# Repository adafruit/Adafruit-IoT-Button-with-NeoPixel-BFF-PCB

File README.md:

## Adafruit IoT Button with NeoPixel BFF PCB

<a href="http://www.adafruit.com/products/5666"><br/>
Click here to purchase one from the Adafruit shop</a>

PCB files for the Adafruit IoT Button with NeoPixel BFF. 

Format is EagleCAD schematic and board layout
* https://www.adafruit.com/product/5666

### Description

Our QT Py boards are a great way to make very small microcontroller projects that pack a ton of power - and now we have a way for you to quickly add a chunky 12mm tactile button with a NeoPixel. It's an excellent way to create simple 'IoT Button' type projects with basic interactivity.

We call this the Adafruit IoT Button with NeoPixel BFF - a "Best Friend Forever". When you were a kid you may have learned about the "buddy" system, well this product is kinda like that! A board that will watch your QT Py's back and give it more capabilities.

This PCB is designed to fit onto the back of any QT Py or Xiao board, it can be soldered into place or use pin and socket headers to make it removable. Onboard is a 12mm tactile button with a nice large actuator, above is a 3.5mm RGB NeoPixel.

We include some header that you can solder to your QT Py. You can also pick up an Itsy Bitsy short female header kit to make it removable but compact, you'll just need to trim down the headers to 7 pins long.

Comes as an assembled and tested PCB
For any QT Py or Xiao boards
Tactile switch momentarily connects A2  to ground when pressed - can cut/re-wire an onboard jumper to change pins if desired. Don't forget to enable an internal pull-up resistor on A2 or whatever pin you use.,
Single NeoPixel on GPIO A3 - can cut/re-wire an onboard jumper to change pins if desired.
QT Py is not included.

### License

Adafruit invests time and resources providing this open source design, please support Adafruit and open-source hardware by purchasing products from [Adafruit](https://www.adafruit.com)!

Designed by Limor Fried/Ladyada for Adafruit Industries.

Creative Commons Attribution/Share-Alike, all text above must be included in any redistribution. 
See license.txt for additional details.

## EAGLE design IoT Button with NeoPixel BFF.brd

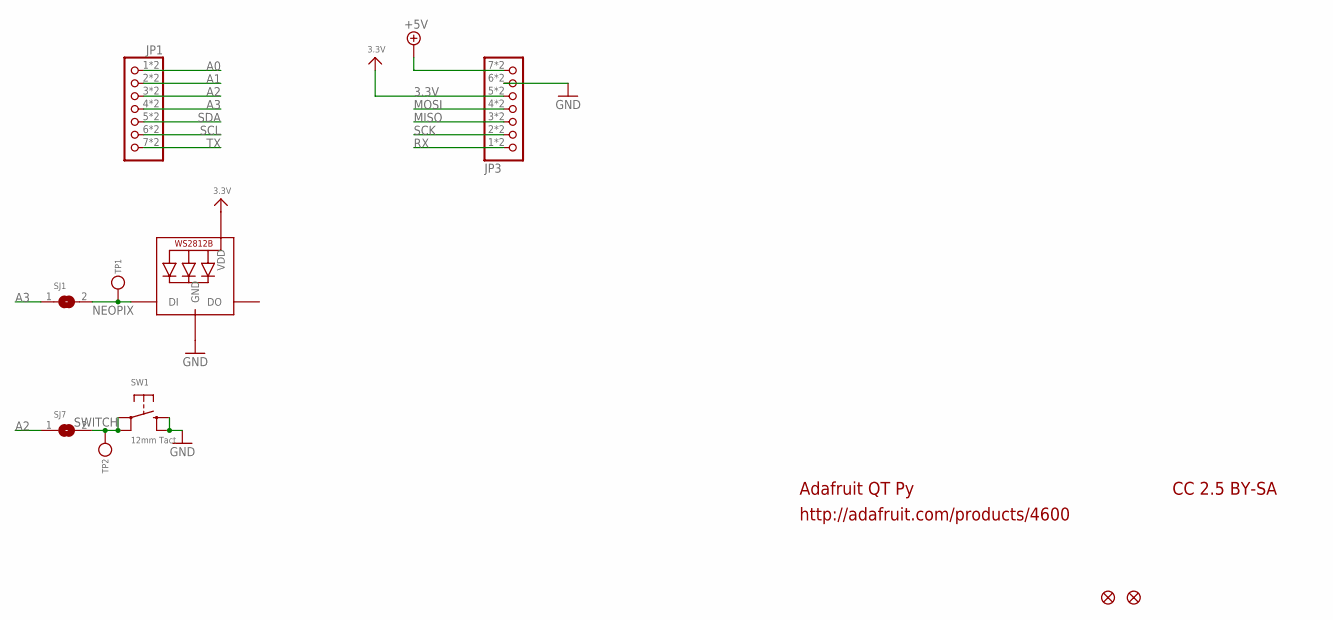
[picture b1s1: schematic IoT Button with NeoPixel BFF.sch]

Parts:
JP1, JP3: HEADER-1X7_CASTEL; 1X07_CASTEL
LED1: WS2812B_3535FULL; LED3535_FULLPADS
SJ1, SJ7: SOLDERJUMPERCLOSED; SOLDERJUMPER_CLOSEDWIRE
SW1: 12mm Tact; B3F-40XX-SMT
TP1, TP2: TESTPOINT1.5X2.0MM_NOCREAM; PAD-1.5X2.0
U$6, U$8: FIDUCIAL_1MM

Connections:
3.3V: JP3.5, JP3.5C (5), LED1.2 (VDD)
+5V: JP3.7, JP3.7C (7)
A0: JP1.1, JP1.1C (1)
A1: JP1.2, JP1.2C (2)
A2: JP1.3, JP1.3C (3), SJ7.1
A3: JP1.4, JP1.4C (4), SJ1.1
GND: JP3.6, JP3.6C (6), LED1.4 (GND), SW1.P$3 (S), SW1.P$4 (S1)
MISO: JP3.3, JP3.3C (3)
MOSI: JP3.4, JP3.4C (4)
NEOPIX: LED1.1 (DI), SJ1.2, TP1.P$1
RX: JP3.1, JP3.1C (1)
SCK: JP3.2, JP3.2C (2)
SCL: JP1.6, JP1.6C (6)
SDA: JP1.5, JP1.5C (5)
SWITCH: SJ7.2, SW1.P$1, SW1.P$2 (P1), TP2.P$1
TX: JP1.7, JP1.7C (7)

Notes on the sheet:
Adafruit QT Py
http://adafruit.com/products/4600
CC 2.5 BY-SA

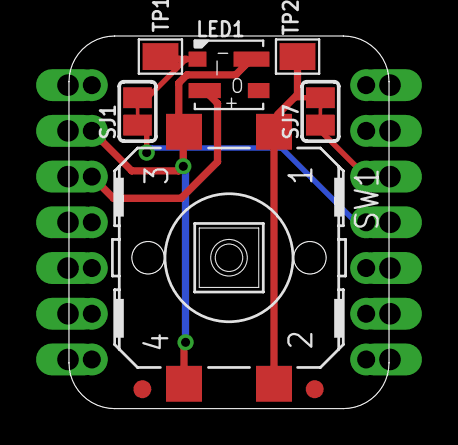
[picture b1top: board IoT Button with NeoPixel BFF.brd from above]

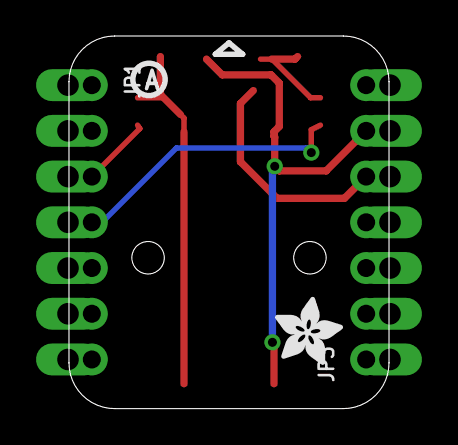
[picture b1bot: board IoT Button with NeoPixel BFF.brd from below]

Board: 2 copper layers, 17.8 x 20.7 mm, 16 parts (4 on the bottom side), 16 nets.

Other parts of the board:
PLABEL1: PLABEL1
PLABEL3: PLABEL3
PLABEL6: PLABEL6
PLABEL14: PLABEL14
U$2: ADAFRUIT_3.5MM
U$3: PCBFEAT-REV-040

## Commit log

2023-01-12 adding cookiecutter output

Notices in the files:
parts and their libraries:
microbuilder: This work is placed in the public domain, and may be freely used for commercial and non-commercial work with the following conditions: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
